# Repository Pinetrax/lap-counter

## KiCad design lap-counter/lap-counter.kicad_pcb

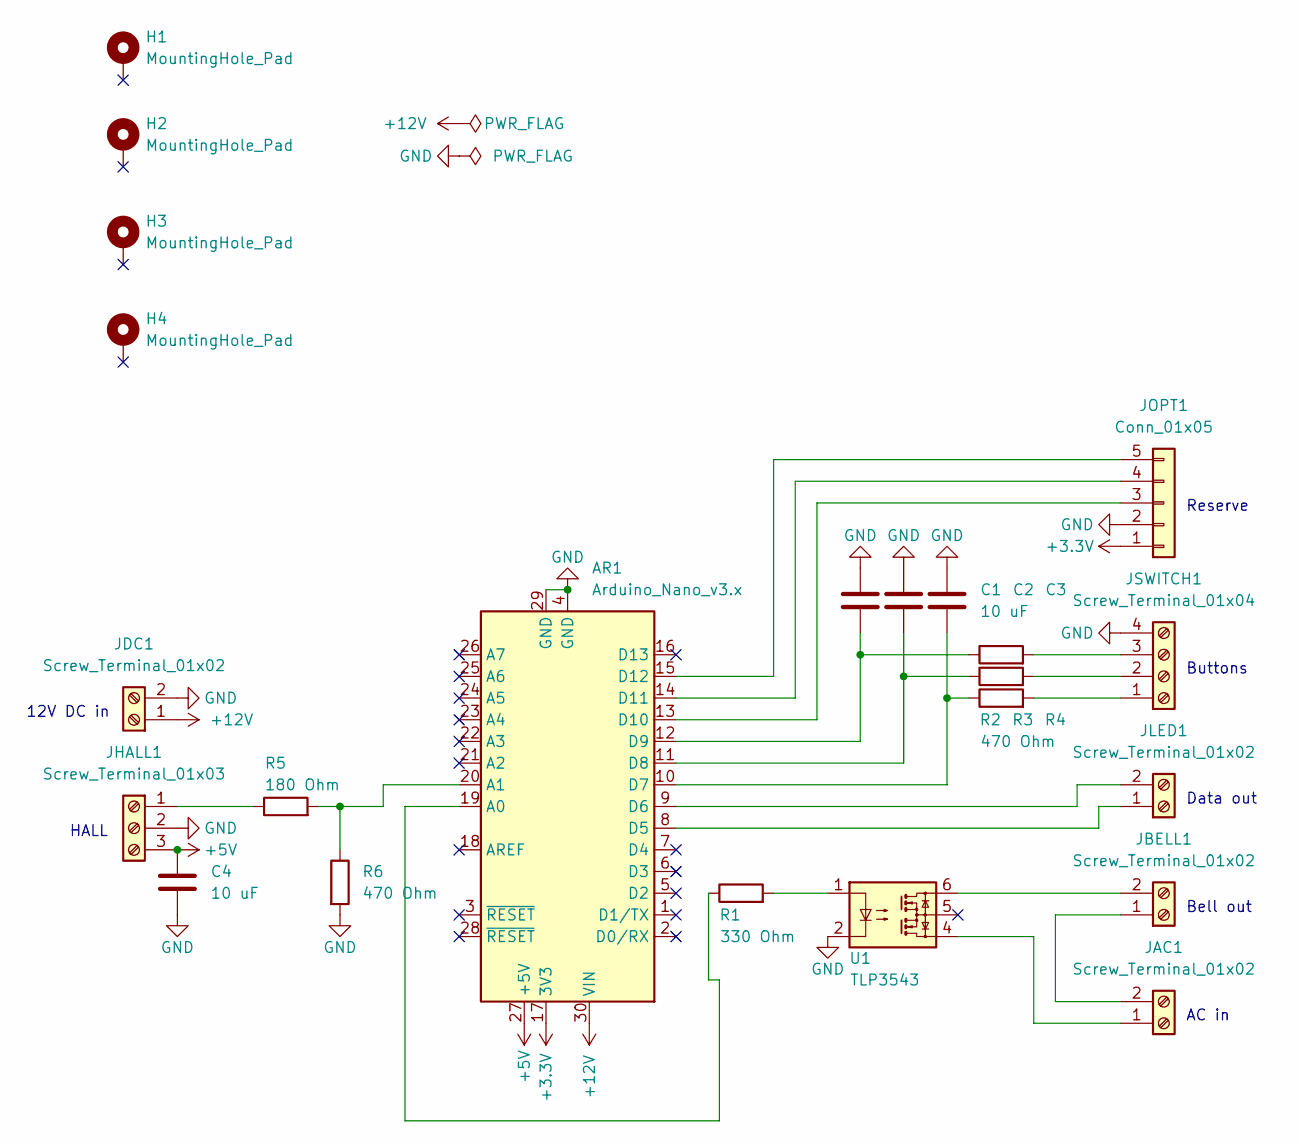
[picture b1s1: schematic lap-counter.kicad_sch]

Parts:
AR1: Arduino_Nano_v3.x; Arduino_Nano
C1, C2, C3, C4: 10 uF; C_0805_2012Metric
H1, H2, H3, H4: MountingHole_Pad; MountingHole_4mm
JAC1: Screw_Terminal_01x02; Molex_Micro-Fit_3.0_43650-0215_1x02_P3.00mm_Vertical
JBELL1: Screw_Terminal_01x02; Molex_Micro-Fit_3.0_43650-0215_1x02_P3.00mm_Vertical
JDC1: Screw_Terminal_01x02; Molex_Micro-Fit_3.0_43650-0215_1x02_P3.00mm_Vertical
JHALL1: Screw_Terminal_01x03; Molex_Micro-Fit_3.0_43650-0315_1x03_P3.00mm_Vertical
JLED1: Screw_Terminal_01x02; Molex_Micro-Fit_3.0_43650-0215_1x02_P3.00mm_Vertical
JOPT1: Conn_01x05; Molex_Micro-Fit_3.0_43650-0515_1x05_P3.00mm_Vertical
JSWITCH1: Screw_Terminal_01x04; Molex_Micro-Fit_3.0_43650-0415_1x04_P3.00mm_Vertical
R1: 330 Ohm; R_0805_2012Metric
R2, R3, R4, R6: 470 Ohm; R_0805_2012Metric
R5: 180 Ohm; R_0805_2012Metric
U1: TLP3543; DIP-6_W7.62mm

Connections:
+3.3V: AR1.17 (3V3), JOPT1.1
+5V: AR1.27 (+5V), C4.2, JHALL1.3
+12V: AR1.30 (VIN), JDC1.1
GND: AR1.4 (GND), AR1.29 (GND), C1.2, C2.2, C3.2, C4.1, JDC1.2, JHALL1.2, JOPT1.2, JSWITCH1.4, R6.2, U1.2
unnamed: AR1.8 (D5), JLED1.1
unnamed: AR1.9 (D6), JLED1.2
unnamed: AR1.10 (D7), C3.1, R4.1
unnamed: AR1.11 (D8), C2.1, R3.1
unnamed: AR1.12 (D9), C1.1, R2.1
unnamed: AR1.13 (D10), JOPT1.3
unnamed: AR1.14 (D11), JOPT1.4
unnamed: AR1.15 (D12), JOPT1.5
unnamed: AR1.19 (A0), R1.1
unnamed: AR1.20 (A1), R5.2, R6.1
unnamed: JAC1.1, U1.4
unnamed: JAC1.2, JBELL1.1
unnamed: JBELL1.2, U1.6
unnamed: JHALL1.1, R5.1
unnamed: JSWITCH1.1, R4.2
unnamed: JSWITCH1.2, R3.2
unnamed: JSWITCH1.3, R2.2
unnamed: R1.2, U1.1

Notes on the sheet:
Reserve
Buttons
HALL
12V DC in
AC in
Bell out
Data out

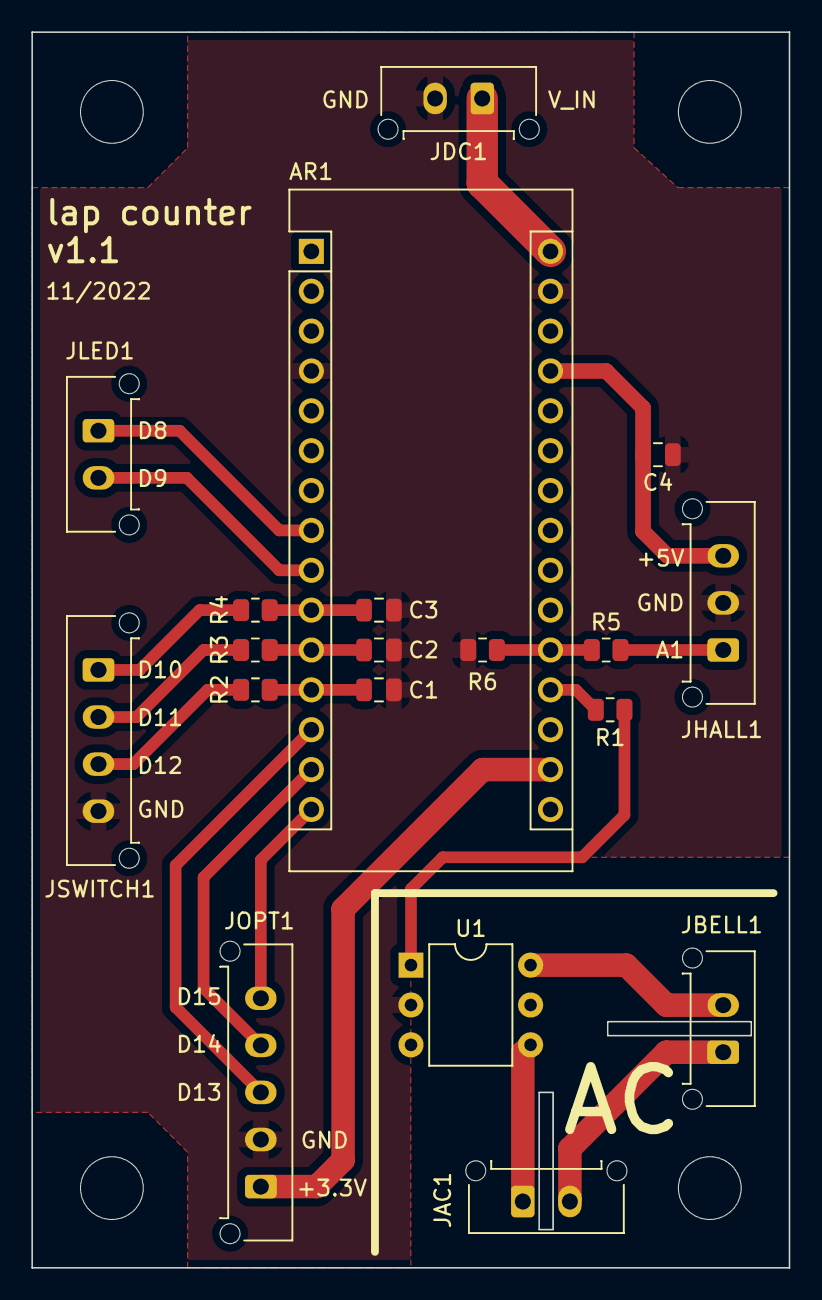
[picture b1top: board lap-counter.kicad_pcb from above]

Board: 2 copper layers, 48.3 x 78.7 mm, 23 parts (0 on the bottom side), 22 nets.

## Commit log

2022-11-27 Add first version of PCB design
2022-11-27 Improve air gap for fabrication
2022-11-27 Optimize trace layout and ground plane
2022-11-27 Raise version to v0.2
2022-11-27 Review and raise version to v1.0
2022-11-27 Add missing changes to last commit
2022-11-28 Raise version to 1.1 with minor improvements, use gitignore
2022-11-28 Remove backup files
